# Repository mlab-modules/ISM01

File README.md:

# ISM01 - Si1060 EZRadioPRO Transceiver

The ISM01 is a high-performance wireless transceiver designed for long-distance data transmission. The module is based on the [Si4463 chip](https://www.silabs.com/wireless/proprietary/ezradiopro-sub-ghz-ics/device.si4463?tab=specs) from Silicon Labs, which is part of the EZRadioPRO family. With its wide frequency range and output power, it is ideal for robust and reliable wireless communication applications. 

ISM01A can operate on the open 433 or 868 MHz frequencies, which are popular in many applications.

## Parameters

- Based on the Si1060 microcontroller integrating the Si4463 transceiver
- Chip frequency range: 142 to 1050 MHz, with the ability to operate on the open 433 or 868 MHz frequencies
- Chip output power: -20 to 20 dBm
- The Si4463 chip includes a programmable block capable of controlling radio settings and supports the SPI interface
- Power supply: 5-12V with integrated 3.3V stabilizer
- Communication: UART, SPI, GPIO
- Accessible GPIO signals directly from the transceiver
- Status indication: Two LEDs controlled from the Si chip
- Antenna connectors: MCX for RX and TX antennas. For bidirectional communication with a single antenna, connecting the [RFSWITCH module](www.mlab.cz/module/RFSWITCH01/) is recommended, which serves as an RF switch and enables MIMO 2x2 support. ISM01A can control the RFSWITCH module through GPIO pins

## Possible Applications

The MLAB ISM01A module with the Si4463 transceiver is suitable for various applications. It can be used in areas such as:

- **Remote Control**: The module can be used for wireless control of various devices, such as drones, RC cars, or home automation.
- **Data Links**: With prepared firmware, the module can function as a [SiK data communication link](https://ardupilot.org/copter/docs/common-sik-telemetry-radio.html), which can transmit [MAVLink packets](https://mavlink.io/en/). MAVLink is a protocol designed for communication with unmanned vehicles and is supported by the most widespread autopilots Ardupilot and PX4. This is ideal for applications that require wireless data transmission.
- **Wireless Sensor Networks**: The module can be used to create wireless sensor networks in IoT applications.

> Based on this module, the company [ThunderFly](https://www.thunderfly.cz) has developed a [TFSIK01](https://docs.thunderfly.cz/avionics/TFSIK01/) optimized for use on drones, which combines this ISM01A module, [RFSWITCH01](https://mlab.cz/module/RFSWITCH01/), and additional RF filters and LNA. More information about this TFSIK01 module can be found [here](https://github.com/ThunderFly-aerospace/TFSIK01/).

## Links to Related Resources

- [Silicon Labs Si4463 Product Page](https://www.silabs.com/wireless/proprietary/ezradiopro-sub-ghz-ics/device.si4463?tab=specs)
- [Si4463 Datasheet](https://www.silabs.com/documents/public/data-sheets/Si4464-63-61-60.pdf)
- [MavLink Protocol](https://mavlink.io/en/)
- [SiK Radio](https://ardupilot.org/copter/docs/common-sik-telemetry-radio.html)
- [EZRADioPRO Family](https://www.silabs.com/wireless/proprietary/ezradiopro-sub-ghz-ics)
- [TFSIK01 Module by ThunderFly](https://github.com/ThunderFly-aerospace/TFSIK01/)

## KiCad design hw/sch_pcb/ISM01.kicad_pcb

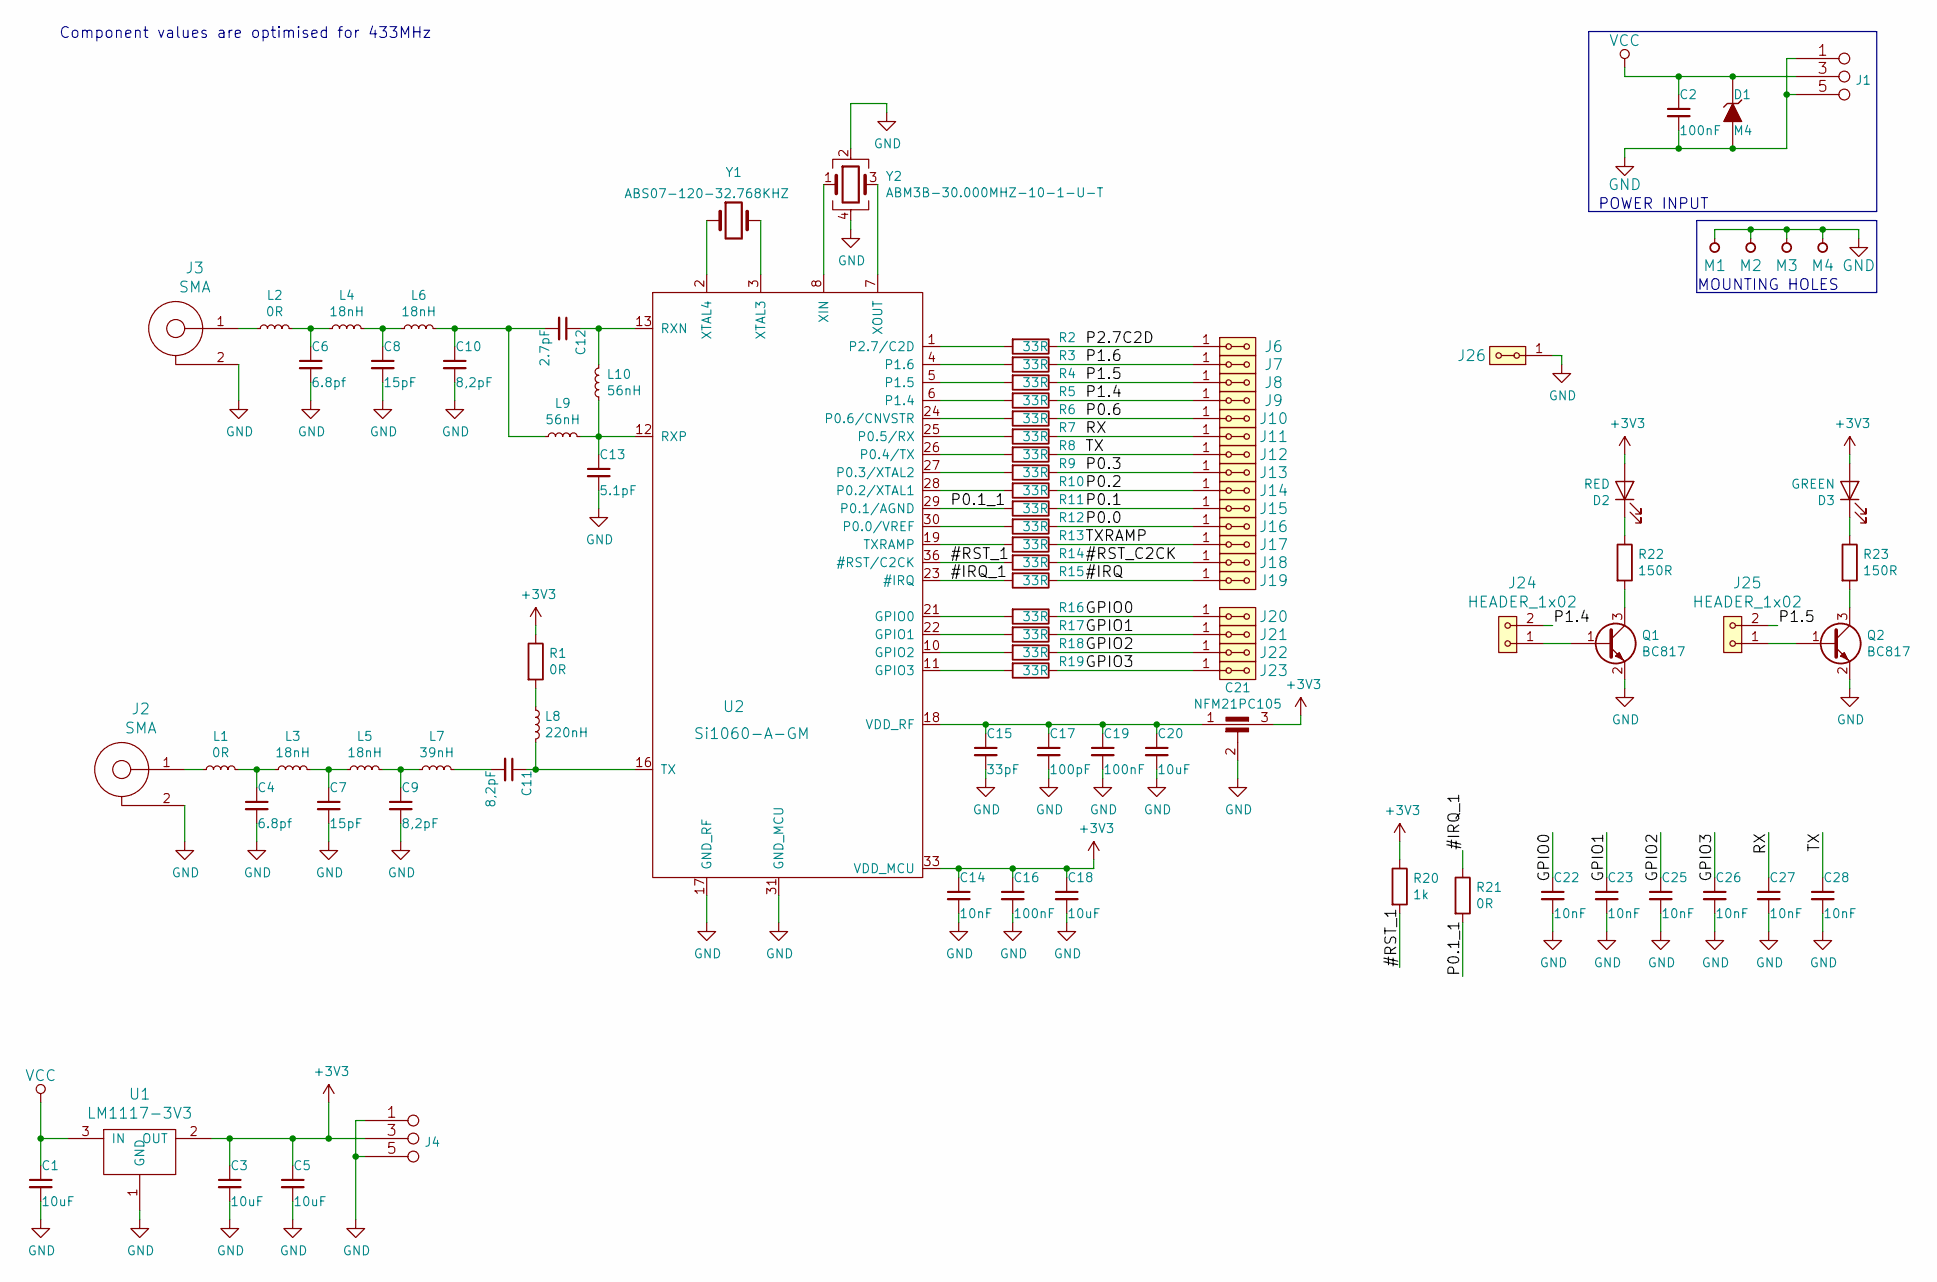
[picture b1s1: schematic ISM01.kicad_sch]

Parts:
C1, C3, C5, C18, C20: 10uF; SMD-0805
C2, C16, C19: 100nF; SMD-0805
C4, C6: 6.8pf; SMD-0805
C7, C8: 15pF; SMD-0805
C9, C10, C11: 8,2pF; SMD-0805
C12: 2.7pF; SMD-0805
C13: 5.1pF; SMD-0805
C14, C22, C23, C25, C26, C27, C28: 10nF; SMD-0805
C15: 33pF; SMD-0805
C17: 100pF; SMD-0805
C21: NFM21PC105; FIR1
D1: M4; Diode-MiniMELF_Standard
D2: RED; LED_1206
D3: GREEN; LED_1206
J1, J4: JUMP_3X2; Straight_2x03
J2, J3: SMA; SMA6251A13G50
J6, J7, J8, J9, J10, J11, J12, J13, J14, J15, J16, J17, J18, J19, J20, J21, J22, J23, J26: HEADER_2x01_PARALLEL; Straight_2x01
J24, J25: HEADER_1x02; Straight_1x02
L1, L2: 0R; SMD-0805
L3, L4, L5, L6: 18nH; SMD-0805
L7: 39nH; SMD-0805
L8: 220nH; SMD-0805
L9, L10: 56nH; SMD-0805
M1, M2, M3, M4: HOLE; MountingHole_3mm
Q1, Q2: BC817; SOT-23
R1, R21: 0R; SMD-0805
R2, R3, R4, R5, R6, R7, R8, R9, R10, R11, R12, R13, R14, R15, R16, R17, R18, R19: 33R; SMD-0805
R20: 1k; SMD-0805
R22, R23: 150R; SMD-0805
U1: LM1117-3V3; SOT-223
U2: Si1060-A-GM; QFN-36-1EP_5x6mm_P0.5mm_EP3.6x4.1mm_ThermalVias
Y1: ABS07-120-32.768KHZ; ABS07
Y2: ABM3B-30.000MHZ-10-1-U-T; Crystal_SMD_Abracon_ABM3B-4Pin_5.0x3.2mm

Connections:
+3V3: C3.1, C5.1, C14.1, C16.1, C18.1, C21.3, D2.2 (A), D3.2 (A), J4.3 (4), J4.4, R1.1, R20.1, U1.2 (OUT), U1.4 (OUT), U2.33 (VDD_MCU)
/#IRQ: J19.1, J19.2, R15.1
/#IRQ_1: R15.2, R21.1, U2.23 (#IRQ)
/#RST_1: R14.2, R20.2, U2.36 (#RST/C2CK)
/#RST_C2CK: J18.1, J18.2, R14.1
/GPIO0: C22.1, J20.1, J20.2, R16.1
/GPIO1: C23.1, J21.1, J21.2, R17.1
/GPIO2: C25.1, J22.1, J22.2, R18.1
/GPIO3: C26.1, J23.1, J23.2, R19.1
/P0.0: J16.1, J16.2, R12.1
/P0.1: J15.1, J15.2, R11.1
/P0.1_1: R11.2, R21.2, U2.29 (P0.1/AGND)
/P0.2: J14.1, J14.2, R10.1
/P0.3: J13.1, J13.2, R9.1
/P0.6: J10.1, J10.2, R6.1
/P1.4: J9.1, J9.2, J24.2, R5.1
/P1.5: J8.1, J8.2, J25.2, R4.1
/P1.6: J7.1, J7.2, R3.1
/P2.7C2D: J6.1, J6.2, R2.1
/RX: C27.1, J11.1, J11.2, R7.1
/TX: C28.1, J12.1, J12.2, R8.1
/TXRAMP: J17.1, J17.2, R13.1
GND: C1.2, C2.2, C3.2, C4.2, C5.2, C6.2, C7.2, C8.2, C9.2, C10.2, C13.2, C14.2, C15.2, C16.2, C17.2, C18.2, C19.2, C20.2, C21.2, C22.2, C23.2, C25.2, C26.2, C27.2, C28.2, D1.2 (A), J1.1 (2), J1.2, J1.5 (6), J1.6, J2.2, J3.2, J4.1 (2), J4.2, J4.5 (6), J4.6, J26.1, J26.2, M1.1, M2.1, M3.1, M4.1, Q1.2 (E), Q2.2 (E), U1.1 (GND), U2.9 (GND_RF), U2.14 (GND_RF), U2.15 (GND_RF), U2.17 (GND_RF), U2.31 (GND_MCU), U2.37 (GND_RF), Y2.2, Y2.4
unnamed: C4.1, L1.2, L3.1
unnamed: C6.1, L2.2, L4.1
unnamed: C7.1, L3.2, L5.1
unnamed: C8.1, L4.2, L6.1
unnamed: C9.1, L5.2, L7.1
unnamed: C10.1, C12.2, L6.2, L9.1
unnamed: C11.1, L8.2, U2.16 (TX)
unnamed: C11.2, L7.2
unnamed: C12.1, L10.2, U2.13 (RXN)
unnamed: C13.1, L9.2, L10.1, U2.12 (RXP)
unnamed: C15.1, C17.1, C19.1, C20.1, C21.1, U2.18 (VDD_RF), U2.20 (VDD_RF)
unnamed: D2.1 (K), R22.1
unnamed: D3.1 (K), R23.1
unnamed: J2.1, L1.1
unnamed: J3.1, L2.1
unnamed: J24.1, Q1.1 (B)
unnamed: J25.1, Q2.1 (B)
unnamed: L8.1, R1.2
unnamed: Q1.3 (C), R22.2
unnamed: Q2.3 (C), R23.2
unnamed: R2.2, U2.1 (P2.7/C2D)
unnamed: R3.2, U2.4 (P1.6)
unnamed: R4.2, U2.5 (P1.5)
unnamed: R5.2, U2.6 (P1.4)
unnamed: R6.2, U2.24 (P0.6/CNVSTR)
unnamed: R7.2, U2.25 (P0.5/RX)
unnamed: R8.2, U2.26 (P0.4/TX)
unnamed: R9.2, U2.27 (P0.3/XTAL2)
unnamed: R10.2, U2.28 (P0.2/XTAL1)
unnamed: R12.2, U2.30 (P0.0/VREF)
unnamed: R13.2, U2.19 (TXRAMP)
unnamed: R16.2, U2.21 (GPIO0)
unnamed: R17.2, U2.22 (GPIO1)
unnamed: R18.2, U2.10 (GPIO2)
unnamed: R19.2, U2.11 (GPIO3)
unnamed: U2.2 (XTAL4), Y1.1
unnamed: U2.3 (XTAL3), Y1.2
unnamed: U2.7 (XOUT), Y2.3
unnamed: U2.8 (XIN), Y2.1
VCC: C1.1, C2.1, D1.1 (K), J1.3 (4), J1.4, U1.3 (IN)

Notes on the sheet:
POWER INPUT
Component values are optimised for 433MHz
MOUNTING HOLES

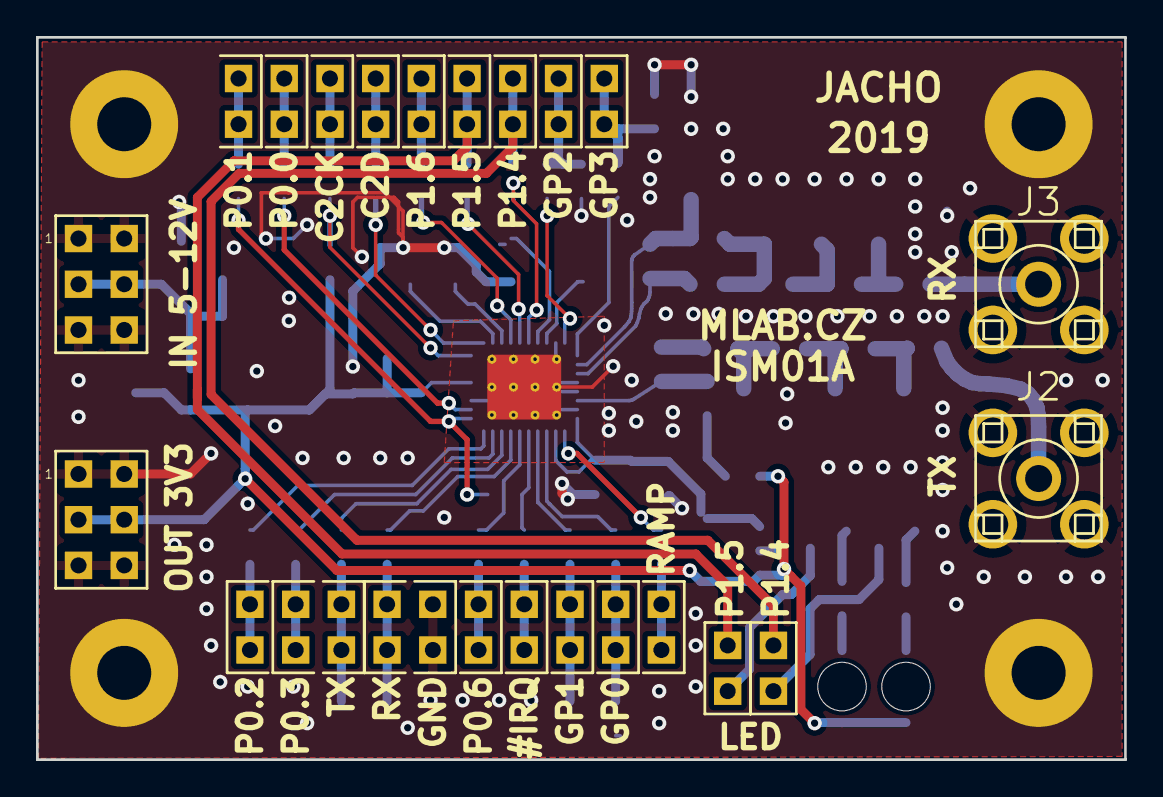
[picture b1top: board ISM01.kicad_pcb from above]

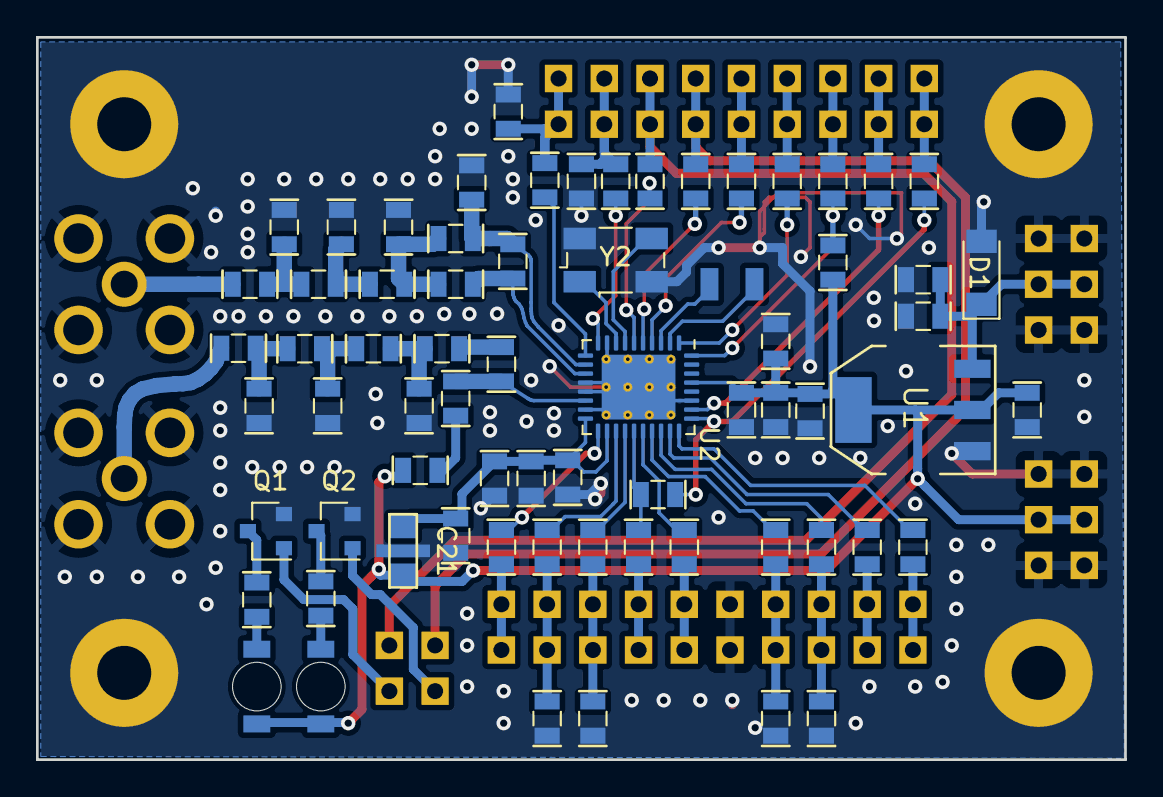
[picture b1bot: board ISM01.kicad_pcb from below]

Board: 2 copper layers, 60.5 x 40.1 mm, 98 parts (69 on the bottom side), 63 nets.

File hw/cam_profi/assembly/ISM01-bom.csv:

Component,Description,Part,References,Value,Footprint,Quantity Per PCB,Datasheet,ust_id
1,,C_Small,C12,2.7pF,SMD-0805,1,,5c70984712875079b91f8b28
2,,C_Small,C13,5.1pF,SMD-0805,1,,5c70984812875079b91f8ba2
3,,C_Small,C4C6,6.8pf,SMD-0805,2,,5c70984712875079b91f8b2e
4,,C_Small,C7C8,15pF,SMD-0805,2,,5c70984712875079b91f8b32
5,,C_Small,C15,33pF,SMD-0805,1,,5c70984712875079b91f8b37
6,,C_Small,C9C10C11,"8,2pF",SMD-0805,3,,5c70984712875079b91f8b2f
7,,C_Small,C17,100pF,SMD-0805,1,,5c70984712875079b91f8b3b
8,,C_Small,C14C22C23C25C26C27C28,10nF,SMD-0805,7,,5c70984712875079b91f8b49
9,,C_Small,C2C16C19,100nF,SMD-0805,3,,5c70984712875079b91f8b4c
10,,C_Small,C1C3C5C18C20,10uF,SMD-0805,5,,5c70984812875079b91f8bbd
11,,EMI_Filter_C,C21,NFM21PC105,FIR1,1,http://www.murata.com/~/media/webrenewal/support/library/cat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,
12,,LED,D3,GREEN,LED_1206,1,,5c70984412875079b91f8895
13,,D_ZENER,D1,M4,Diode-MiniMELF_Standard,1,,5c70984512875079b91f88ac
14,,LED,D2,RED,LED_1206,1,,5c70984412875079b91f8896
15,,HEADER_1x02,J24J25,HEADER_1x02,Straight_1x02,2,,
16,,HEADER_2x01_PARALLEL,J6J7J8J9J10J11J12J13J14J15J16J17J18J19J20J21J22J23J26,HEADER_2x01_PARALLEL,Straight_2x01,19,,
17,,JUMP_3X2,J1J4,JUMP_3X2,Straight_2x03,2,,
18,,SMA,J2J3,SMA,SMA6251A13G50,2,,5c70984412875079b91f87ac
19,,L_Small,L1L2,0R,SMD-0805,2,,5c70984512875079b91f896b
20,,L_Small,L3L4L5L6,18nH,SMD-0805,4,,5c70984412875079b91f8806
21,,L_Small,L7,39nH,SMD-0805,1,,5c70984412875079b91f8809
22,,L_Small,L9L10,56nH,SMD-0805,2,,5c70984812875079b91f8ba4
23,,L_Small,L8,220nH,SMD-0805,1,,5c70984412875079b91f880d
24,,Q_NPN_BEC,Q1Q2,BC817,SOT-23,2,,5c70984712875079b91f8aec
25,,R,R1R21,0R,SMD-0805,2,,5c70984512875079b91f896b
26,,R,R2R3R4R5R6R7R8R9R10R11R12R13R14R15R16R17R18R19,33R,SMD-0805,18,,5c70984512875079b91f8970
27,,R,R22R23,150R,SMD-0805,2,,5c70984512875079b91f897a
28,,R,R20,1k,SMD-0805,1,,5c70984512875079b91f898c
29,,LM1117,U1,LM1117-3V3,SOT-223,1,,5c70984712875079b91f8af9
30,,Si1060-A-GM,U2,Si1060-A-GM,QFN-36-1EP_5x6mm_P0.5mm_EP3.6x4.1mm_ThermalVias,1,https://www.silabs.com/documents/public/data-sheets/Si106x-8x.pdf,5c70984812875079b91f8ba3
31,,Crystal_GND24,Y2,ABM3B-30.000MHZ-10-1-U-T,Crystal_SMD_Abracon_ABM3B-4Pin_5.0x3.2mm,1,,5c70984712875079b91f8ba1
32,,Crystal,Y1,ABS07-120-32.768KHZ,ABS07,1,,5c70984712875079b91f8b1b

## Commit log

2018-11-29 [MLABweb] Documentaion edits; ISM01A
2018-11-29 Edit
2019-02-19 Pokus o zaoblení RF cesty.
2019-02-20 Zakulacení RF cest.
2019-02-20 Vyrovnání izolačních mezer cest.
2019-10-28 Prvni verze layoutu
2019-11-28 Přidání bootloaderu pro modul.
2020-01-21 [MLABweb] Documentation edits; ISM01A
2020-05-04 The basic photos of new modules.
2020-10-28 Fix license.
2020-11-04 Edit 3D model
2020-11-04 Edit images
2022-01-13 Adding a link to datasheet.
2022-04-06 automated commit; add github actions
2022-04-06 Update actions products
2023-02-13 update actions
2023-02-13 Update metadata files
2023-03-06 update workflow
2023-05-25 Update workflow files
2023-07-05 automated commit; rename source files to new naming convence
2023-07-20 aktualizace na kicad 7
2023-09-16 Update image to image_title
2023-09-16 Update status
2023-09-16 Update metadata.yaml
    change title image.
2024-07-03 Update README.md
    Fix typos
2024-07-15 Update README.md
    Explain relevance between Si1060 and Si4463.
2025-02-03 Update project to KiCADv8.
    Fix wrong title block description.
2025-03-13 Pridani application note.
